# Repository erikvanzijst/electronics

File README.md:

# electronics

This is a Pages repo hosted at <https://erikvanzijst.github.io/electronics>.

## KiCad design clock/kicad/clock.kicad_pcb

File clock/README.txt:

https://www.eevblog.com/forum/beginners/using-a-32-768khz-crystal-with-4060-frequency-divider/

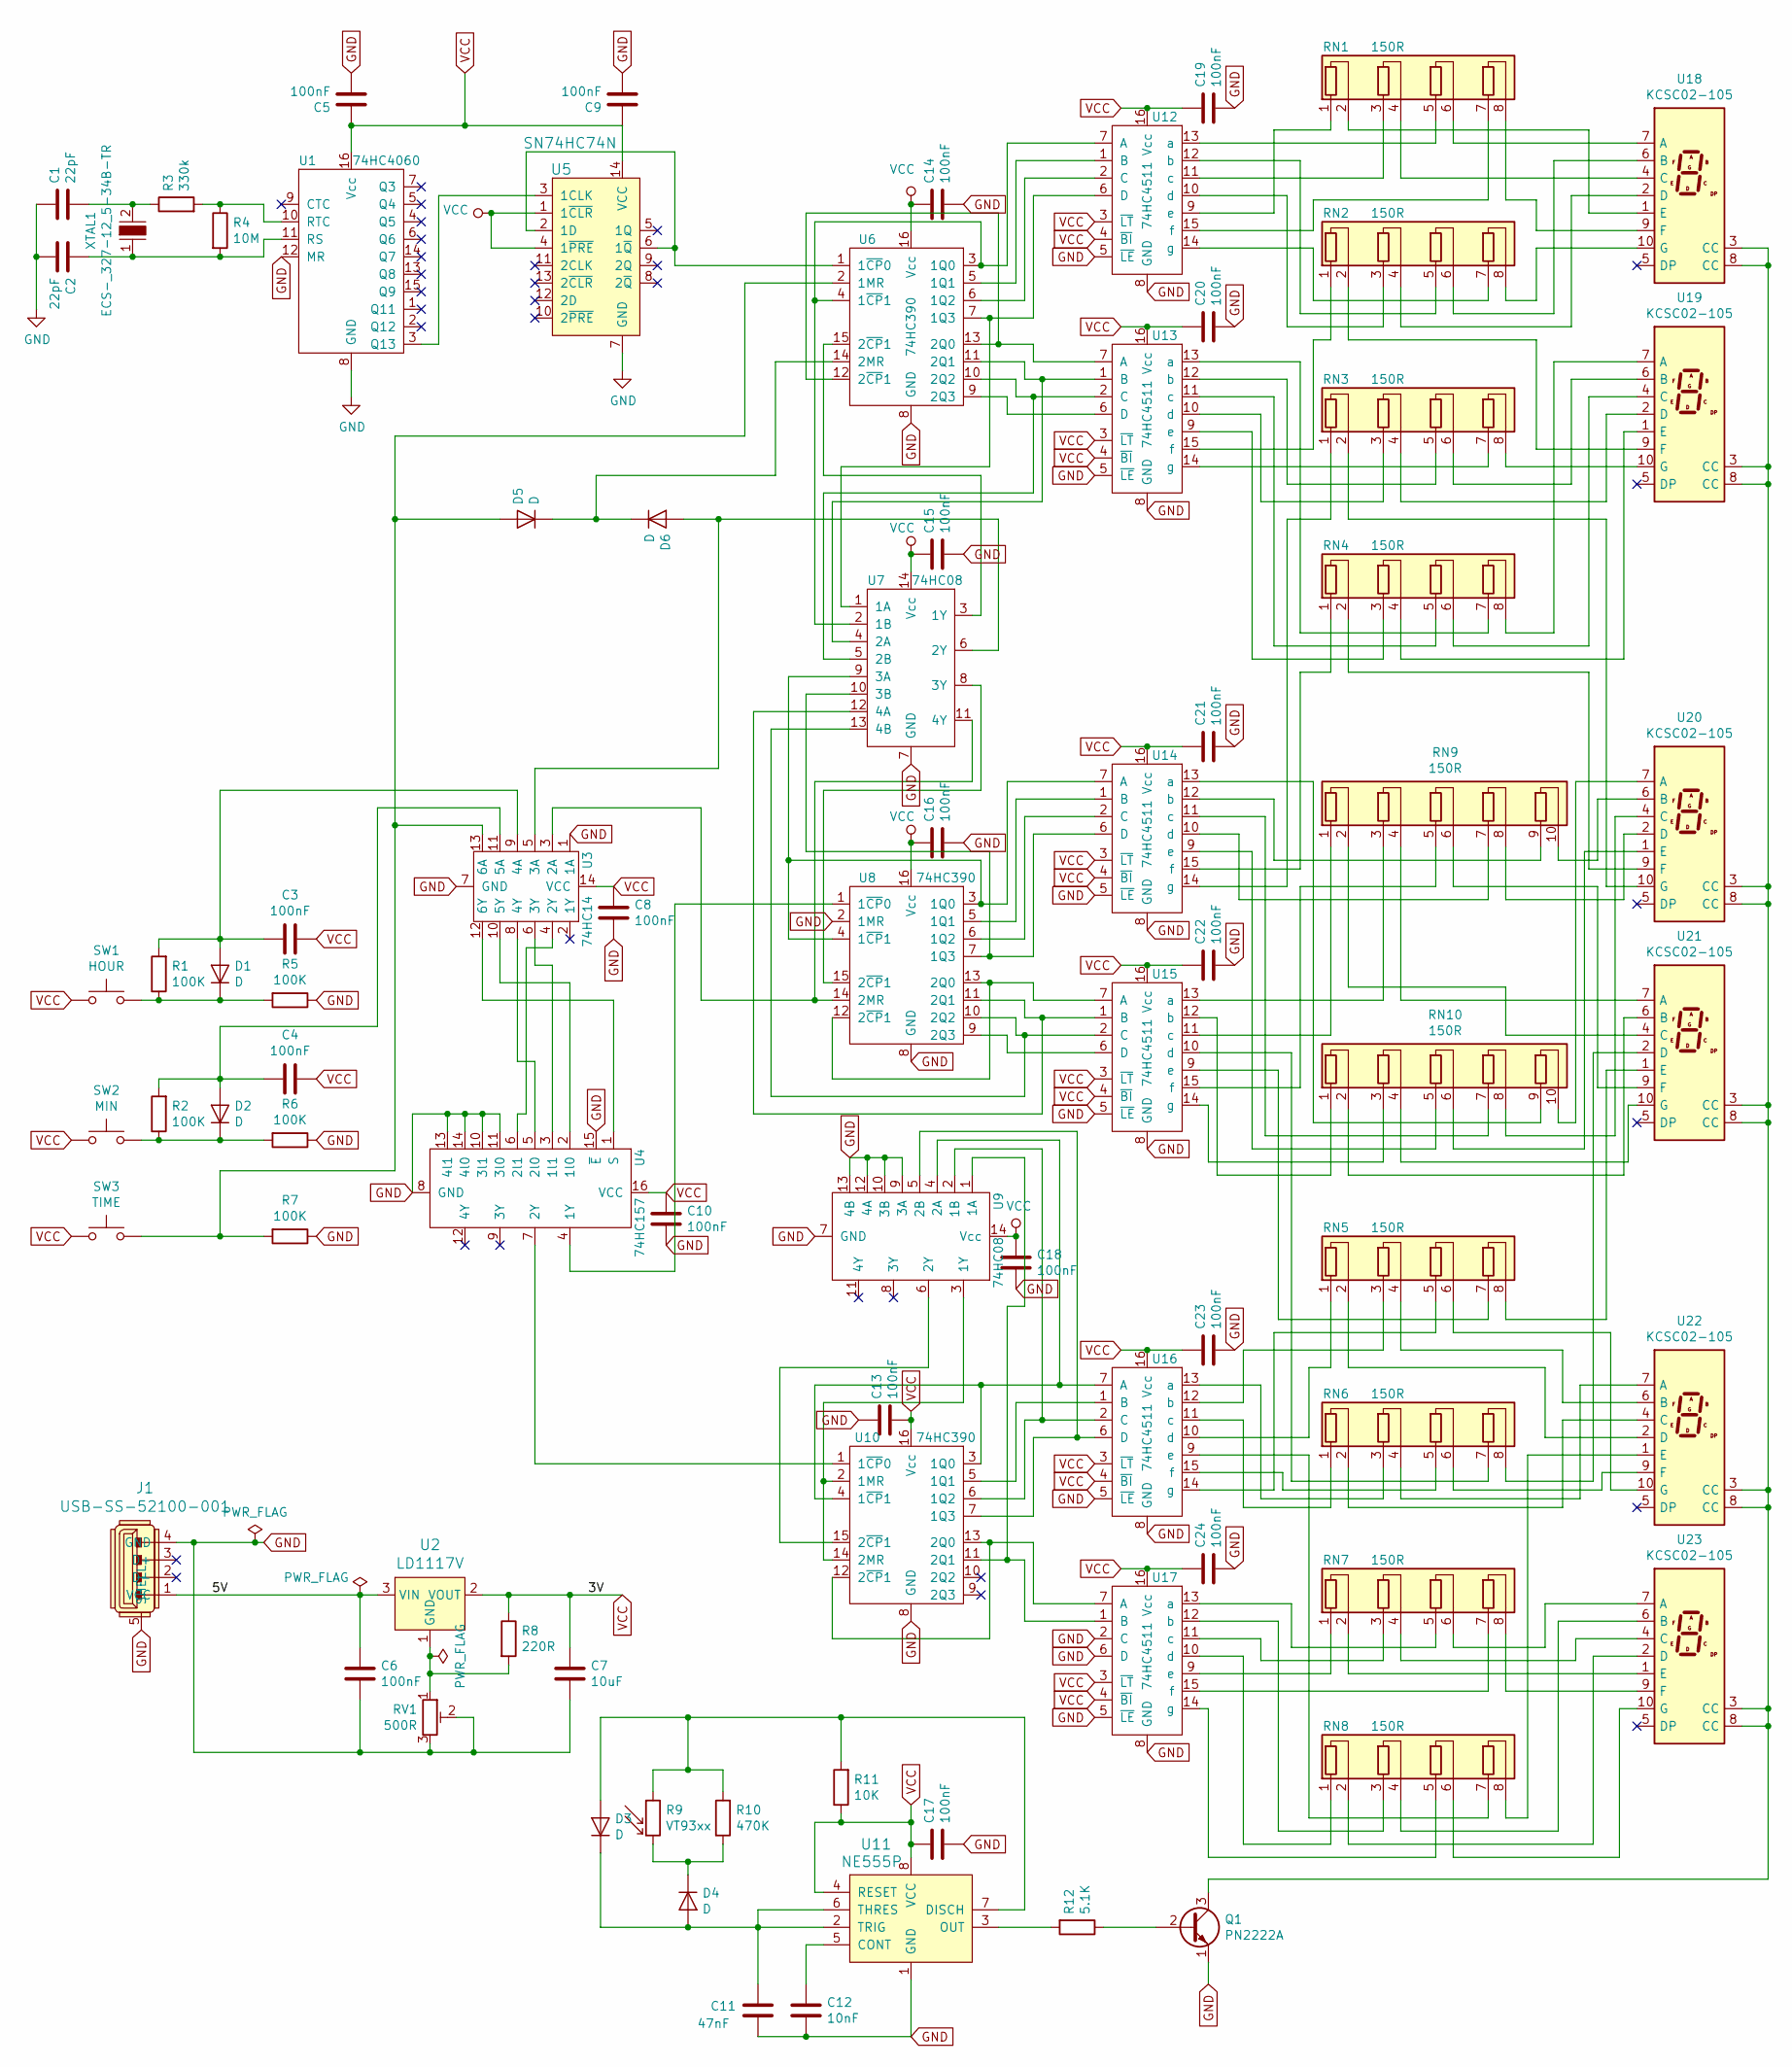
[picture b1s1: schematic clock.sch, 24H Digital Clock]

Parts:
C1, C2: 22pF; C_Disc_D5.0mm_W2.5mm_P2.50mm
C3, C4, C5, C6, C8, C9, C10, C13, C14, C15, C16, C17, C18, C19, C20, C21, C22, C23, C24: 100nF; C_Disc_D5.0mm_W2.5mm_P2.50mm
C7: 10uF; C_Radial_D5.0mm_H11.0mm_P2.00mm
C11: 47nF; C_Disc_D5.0mm_W2.5mm_P2.50mm
C12: 10nF; C_Disc_D5.0mm_W2.5mm_P2.50mm
D1, D2, D3, D4, D5, D6: D; Diode_DO-35_P10mm
J1: USB-SS-52100-001; USB_A_Stewart_SS-52100-001_Horizontal; MPN SS-52100-001; Digi-Key_PN 380-1412-ND
Q1: PN2222A; TO-92_Inline_Wide
R1, R2, R5, R6, R7: 100K; R_Axial_DIN0207_L6.3mm_D2.5mm_P7.62mm_Horizontal
R3: 330k; R_Axial_DIN0207_L6.3mm_D2.5mm_P7.62mm_Horizontal
R4: 10M; R_Axial_DIN0207_L6.3mm_D2.5mm_P7.62mm_Horizontal
R8: 220R; R_Axial_DIN0207_L6.3mm_D2.5mm_P7.62mm_Horizontal
R9: VT93xx; R_LDR_4.9x4.2mm_P2.54mm_Vertical
R10: 470K; R_Axial_DIN0207_L6.3mm_D2.5mm_P7.62mm_Horizontal
R11: 10K; R_Axial_DIN0207_L6.3mm_D2.5mm_P7.62mm_Horizontal
R12: 5.1K; R_Axial_DIN0207_L6.3mm_D2.5mm_P7.62mm_Horizontal
RN1, RN2, RN3, RN4, RN5, RN6, RN7, RN8: 150R; R_Array_SIP8
RN9, RN10: 150R; R_Array_SIP10
RV1: 500R; Potentiometer_Bourns_3339P_Vertical_HandSoldering
SW1: HOUR; SW_PUSH_6mm_H4.3mm
SW2: MIN; SW_PUSH_6mm_H4.3mm
SW3: TIME; SW_PUSH_6mm_H4.3mm
U1: 74HC4060; DIP-16_W7.62mm_Socket
U2: LD1117V; TO-220-3; MPN LD1117V; Digi-Key_PN 497-7310-5-ND
U3: 74HC14; Socket_DIP-14_0.775in_Conn
U4: 74HC157; DIP-16_W7.62mm_Socket
U5: SN74HC74N; Socket_DIP-14_0.775in_Conn; MPN SN74HC74N; Digi-Key_PN 296-1602-5-ND
U6, U8, U10: 74HC390; DIP-16_W7.62mm_Socket
U7, U9: 74HC08; Socket_DIP-14_0.775in_Conn
U11: NE555P; DIP-8_W7.62mm_Socket; MPN NE555P; Digi-Key_PN 296-1411-5-ND
U12, U13, U14, U15, U16, U17: 74HC4511; DIP-16_W7.62mm_Socket
U18, U19, U20, U21, U22, U23: KCSC02-105; 7SegmentLED_LTS6760_LTS6780
XTAL1: ECS-_327-12_5-34B-TR; Crystal_DS26_D2.0mm_L6.0mm_Horizontal; MPN ECS-.327-12.5-34B-TR; Digi-Key_PN XC1617CT-ND

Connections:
/5V: C6.1, J1.1 (VCC), U2.3 (VIN)
GND: C1.1, C2.2, C5.2, C6.2, C7.2, C8.2, C9.2, C10.2, C11.2, C12.2, C13.1, C14.2, C15.2, C16.2, C17.2, C18.2, C19.2, C20.2, C21.2, C22.2, C23.2, C24.2, J1.4 (GND), J1.5 (SHELL), Q1.1 (E), R5.1, R6.1, R7.1, RV1.2, RV1.3, U1.8 (GND), U1.12 (MR), U3.1 (1A), U3.7 (GND), U4.8 (GND), U4.10 (3l1), U4.11 (3l0), U4.13 (4l1), U4.14 (4l0), U4.15 (~E), U5.7 (GND), U6.8 (GND), U7.7 (GND), U8.2 (1MR), U8.8 (GND), U9.7 (GND), U9.9 (3A), U9.10 (3B), U9.12 (4A), U9.13 (4B), U10.8 (GND), U11.1 (GND), U12.5 (~LE), U12.8 (GND), U13.5 (~LE), U13.8 (GND), U14.5 (~LE), U14.8 (GND), U15.5 (~LE), U15.8 (GND), U16.5 (~LE), U16.8 (GND), U17.2 (C), U17.5 (~LE), U17.6 (D), U17.8 (GND)
unnamed: C1.2, R3.1, XTAL1.2
unnamed: C2.1, R4.2, U1.11 (RS), XTAL1.1
unnamed: C3.2, D1.2 (A), R1.2, U3.9 (4A)
unnamed: C4.2, D2.2 (A), R2.2, U3.11 (5A)
unnamed: C11.1, D3.1 (K), D4.2 (A), U11.2 (TRIG), U11.6 (THRES)
unnamed: C12.1, U11.5 (CONT)
unnamed: D1.1 (K), R1.1, R5.2, SW1.2
unnamed: D2.1 (K), R2.1, R6.2, SW2.2
unnamed: D3.2 (A), R9.1, R10.2, R11.2, U11.7 (DISCH)
unnamed: D4.1 (K), R9.2, R10.1
unnamed: D5.1 (K), D6.1 (K), U6.14 (2MR)
unnamed: D5.2 (A), R7.2, SW3.2, U3.13 (6A), U6.2 (1MR)
unnamed: D6.2 (A), U3.5 (3A), U7.6 (2Y)
unnamed: Q1.2 (B), R12.1
unnamed: Q1.3 (C), U18.3 (CC), U18.8 (CC), U19.3 (CC), U19.8 (CC), U20.3 (CC), U20.8 (CC), U21.3 (CC), U21.8 (CC), U22.3 (CC), U22.8 (CC), U23.3 (CC), U23.8 (CC)
unnamed: R3.2, R4.1, U1.10 (RTC)
unnamed: R8.2, RV1.1, U2.1 (GND)
unnamed: R12.2, U11.3 (OUT)
unnamed: RN1.1 (R1.1), U12.9 (e)
unnamed: RN1.2 (R1.2), U18.1 (E)
unnamed: RN1.3 (R2.1), U12.11 (c)
unnamed: RN1.4 (R2.2), U18.4 (C)
unnamed: RN1.5 (R3.1), U12.13 (a)
unnamed: RN1.6 (R3.2), U18.7 (A)
unnamed: RN1.7 (R4.1), U12.15 (f)
unnamed: RN1.8 (R4.2), U18.9 (F)
unnamed: RN2.1 (R1.1), U13.15 (f)
unnamed: RN2.2 (R1.2), U19.9 (F)
unnamed: RN2.3 (R2.1), U12.10 (d)
unnamed: RN2.4 (R2.2), U18.2 (D)
unnamed: RN2.5 (R3.1), U12.12 (b)
unnamed: RN2.6 (R3.2), U18.6 (B)
unnamed: RN2.7 (R4.1), U12.14 (g)
unnamed: RN2.8 (R4.2), U18.10 (G)
unnamed: RN3.1 (R1.1), U14.14 (g)
unnamed: RN3.2 (R1.2), U20.10 (G)
unnamed: RN3.3 (R2.1), U13.10 (d)
unnamed: RN3.4 (R2.2), U19.2 (D)
unnamed: RN3.5 (R3.1), U13.12 (b)
unnamed: RN3.6 (R3.2), U19.6 (B)
unnamed: RN3.7 (R4.1), U13.14 (g)
unnamed: RN3.8 (R4.2), U19.10 (G)
unnamed: RN4.1 (R1.1), U14.15 (f)
unnamed: RN4.2 (R1.2), U20.9 (F)
unnamed: RN4.3 (R2.1), U13.9 (e)
unnamed: RN4.4 (R2.2), U19.1 (E)
unnamed: RN4.5 (R3.1), U13.11 (c)
unnamed: RN4.6 (R3.2), U19.4 (C)
unnamed: RN4.7 (R4.1), U13.13 (a)
unnamed: RN4.8 (R4.2), U19.7 (A)
unnamed: RN5.1 (R1.1), U16.10 (d)
unnamed: RN5.2 (R1.2), U22.2 (D)
unnamed: RN5.3 (R2.1), U16.12 (b)
unnamed: RN5.4 (R2.2), U22.6 (B)
unnamed: RN5.5 (R3.1), U16.14 (g)
unnamed: RN5.6 (R3.2), U22.10 (G)
unnamed: RN5.7 (R4.1), U15.9 (e)
unnamed: RN5.8 (R4.2), U21.1 (E)
unnamed: RN6.1 (R1.1), U16.11 (c)
unnamed: RN6.2 (R1.2), U22.4 (C)
unnamed: RN6.3 (R2.1), U16.13 (a)
unnamed: RN6.4 (R2.2), U22.7 (A)
unnamed: RN6.5 (R3.1), U16.15 (f)
unnamed: RN6.6 (R3.2), U22.9 (F)
unnamed: RN6.7 (R4.1), U15.10 (d)
unnamed: RN6.8 (R4.2), U21.2 (D)
unnamed: RN7.1 (R1.1), U17.9 (e)
unnamed: RN7.2 (R1.2), U23.1 (E)
unnamed: RN7.3 (R2.1), U17.11 (c)
unnamed: RN7.4 (R2.2), U23.4 (C)
unnamed: RN7.5 (R3.1), U17.13 (a)
unnamed: RN7.6 (R3.2), U23.7 (A)
unnamed: RN7.7 (R4.1), U17.15 (f)
unnamed: RN7.8 (R4.2), U23.9 (F)
unnamed: RN8.1 (R1.1), U17.10 (d)
unnamed: RN8.2 (R1.2), U23.2 (D)
unnamed: RN8.3 (R2.1), U17.12 (b)
unnamed: RN8.4 (R2.2), U23.6 (B)
unnamed: RN8.5 (R3.1), U17.14 (g)
unnamed: RN8.6 (R3.2), U23.10 (G)
unnamed: RN8.7 (R4.1), U16.9 (e)
unnamed: RN8.8 (R4.2), U22.1 (E)
unnamed: RN9.1 (R1.1), U15.11 (c)
unnamed: RN9.2 (R1.2), U21.4 (C)
unnamed: RN9.3 (R2.1), U15.13 (a)
unnamed: RN9.4 (R2.2), U21.7 (A)
unnamed: RN9.5 (R3.1), U15.15 (f)
unnamed: RN9.6 (R3.2), U21.9 (F)
unnamed: RN9.7 (R4.1), U14.10 (d)
unnamed: RN9.8 (R4.2), U20.2 (D)
unnamed: RN9.9 (R5.1), U14.12 (b)
unnamed: RN9.10 (R5.2), U20.6 (B)
unnamed: RN10.1 (R1.1), U15.12 (b)
unnamed: RN10.2 (R1.2), U21.6 (B)
unnamed: RN10.3 (R2.1), U15.14 (g)
unnamed: RN10.4 (R2.2), U21.10 (G)
unnamed: RN10.5 (R3.1), U14.9 (e)
unnamed: RN10.6 (R3.2), U20.1 (E)
unnamed: RN10.7 (R4.1), U14.11 (c)
unnamed: RN10.8 (R4.2), U20.4 (C)
unnamed: RN10.9 (R5.1), U14.13 (a)
unnamed: RN10.10 (R5.2), U20.7 (A)
unnamed: U1.3 (Q13), U5.3 (1CLK)
unnamed: U3.3 (2A), U7.11 (4Y), U8.14 (2MR)
unnamed: U3.4 (2Y), U4.6 (2l1)
unnamed: U3.6 (3Y), U4.3 (1l1)
unnamed: U3.8 (4Y), U4.5 (2l0)
unnamed: U3.10 (5Y), U4.2 (1l0)
unnamed: U3.12 (6Y), U4.1 (S)
unnamed: U4.4 (1Y), U8.1 (1~CP~0)
unnamed: U5.2 (1D), U5.6 (1~Q), U6.1 (1~CP~0)
unnamed: U6.15 (2~CP~1), U7.3 (1Y)
unnamed: U7.8 (3Y), U8.15 (2~CP~1)
unnamed: U4.7 (2Y), U10.1 (1~CP~0)
unnamed: U9.4 (2A), U10.3 (1Q0), U10.4 (1~CP~1), U16.7 (A)
unnamed: U10.5 (1Q1), U16.1 (B)
unnamed: U9.2 (1B), U10.6 (1Q2), U16.2 (C)
unnamed: U9.5 (2B), U10.7 (1Q3), U16.6 (D)
unnamed: U9.1 (1A), U10.11 (2Q1), U17.1 (B)
unnamed: U10.12 (2~CP~1), U10.13 (2Q0), U17.7 (A)
unnamed: U9.3 (1Y), U10.2 (1MR), U10.14 (2MR)
unnamed: U9.6 (2Y), U10.15 (2~CP~1)
unnamed: U6.5 (1Q1), U12.1 (B)
unnamed: U6.6 (1Q2), U12.2 (C)
unnamed: U6.7 (1Q3), U7.1 (1A), U12.6 (D)
unnamed: U6.3 (1Q0), U6.4 (1~CP~1), U7.2 (1B), U12.7 (A)
unnamed: U6.11 (2Q1), U7.4 (2A), U13.1 (B)
unnamed: U6.10 (2Q2), U7.5 (2B), U13.2 (C)
unnamed: U6.9 (2Q3), U13.6 (D)
unnamed: U6.12 (2~CP~1), U6.13 (2Q0), U13.7 (A)
unnamed: U8.5 (1Q1), U14.1 (B)
unnamed: U8.6 (1Q2), U14.2 (C)
unnamed: U7.10 (3B), U8.7 (1Q3), U14.6 (D)
unnamed: U7.9 (3A), U8.3 (1Q0), U8.4 (1~CP~1), U14.7 (A)
unnamed: U7.12 (4A), U8.11 (2Q1), U15.1 (B)
unnamed: U7.13 (4B), U8.10 (2Q2), U15.2 (C)
unnamed: U8.9 (2Q3), U15.6 (D)
unnamed: U8.12 (2~CP~1), U8.13 (2Q0), U15.7 (A)
VCC: C3.1, C4.1, C5.1, C7.1, C8.1, C9.1, C10.1, C13.2, C14.1, C15.1, C16.1, C17.1, C18.1, C19.1, C20.1, C21.1, C22.1, C23.1, C24.1, R8.1, R11.1, SW1.1, SW2.1, SW3.1, U1.16 (Vcc), U2.2 (VOUT), U3.14 (VCC), U4.16 (VCC), U5.1 (1~CLR), U5.4 (1~PRE), U5.14 (VCC), U6.16 (Vcc), U7.14 (Vcc), U8.16 (Vcc), U9.14 (Vcc), U10.16 (Vcc), U11.4 (RESET), U11.8 (VCC), U12.3 (~LT), U12.4 (~BI), U12.16 (Vcc), U13.3 (~LT), U13.4 (~BI), U13.16 (Vcc), U14.3 (~LT), U14.4 (~BI), U14.16 (Vcc), U15.3 (~LT), U15.4 (~BI), U15.16 (Vcc), U16.3 (~LT), U16.4 (~BI), U16.16 (Vcc), U17.3 (~LT), U17.4 (~BI), U17.16 (Vcc)

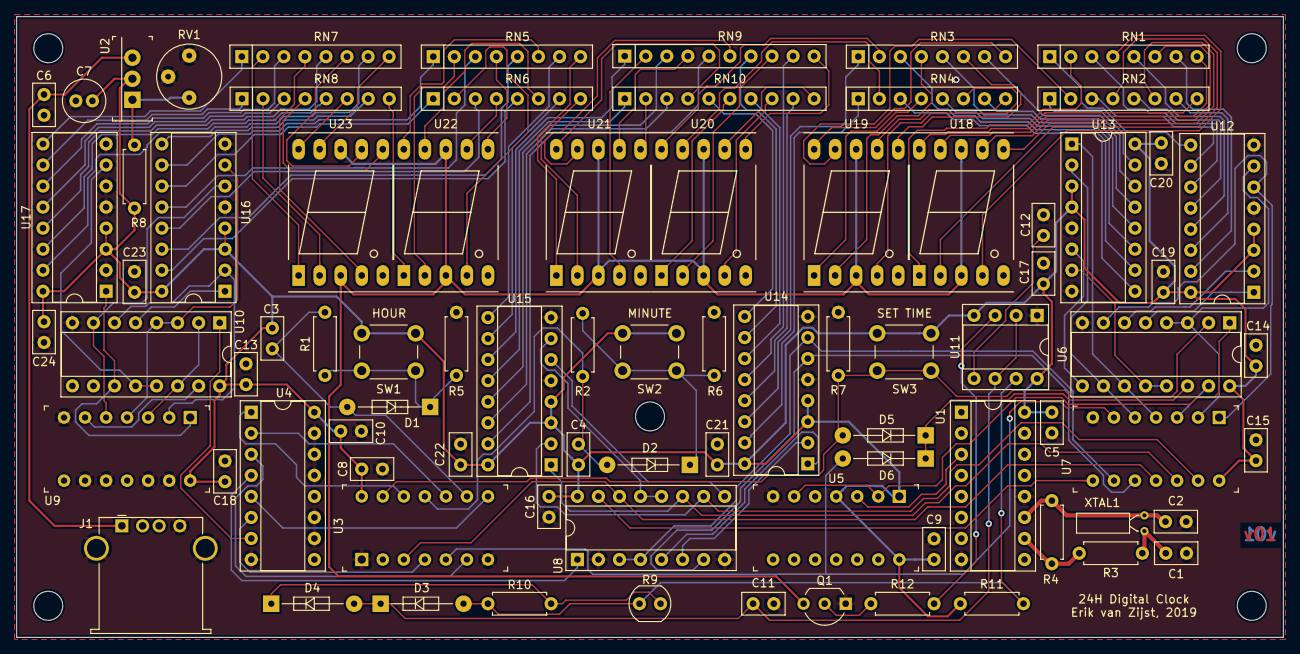
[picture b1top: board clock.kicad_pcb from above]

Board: 2 copper layers, 152.9 x 74.9 mm, 82 parts (0 on the bottom side), 141 nets.

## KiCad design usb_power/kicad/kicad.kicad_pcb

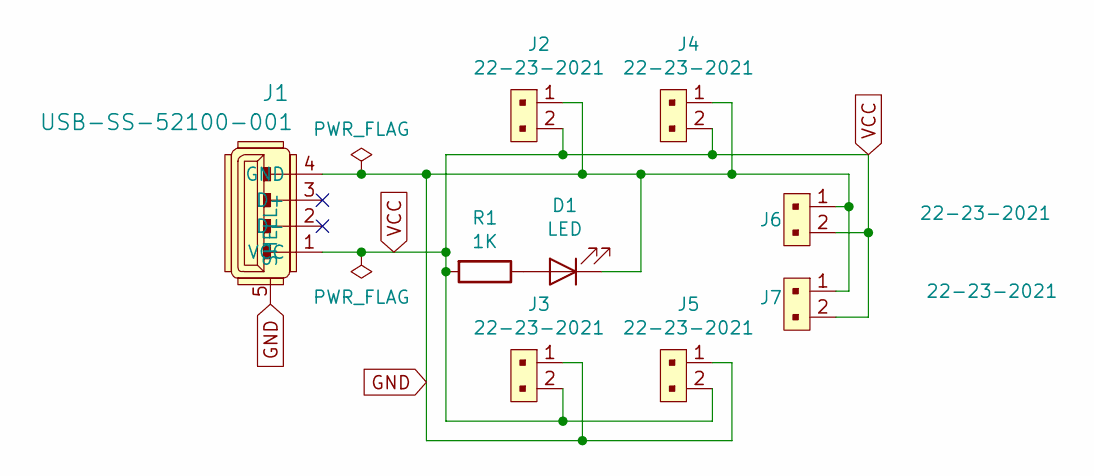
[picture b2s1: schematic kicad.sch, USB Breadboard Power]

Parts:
D1: LED; LED_D5.0mm_IRGrey
J1: USB-SS-52100-001; USB_A_Stewart_SS-52100-001_Horizontal; MPN SS-52100-001; Digi-Key_PN 380-1412-ND
J2, J3, J4, J5, J6, J7: 22-23-2021; PinHeader_1x2_P2.54mm_Drill1.02mm; MPN 22-23-2021; Digi-Key_PN WM4200-ND
R1: 1K; R_Axial_DIN0207_L6.3mm_D2.5mm_P7.62mm_Horizontal

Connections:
GND: D1.1 (K), J1.4 (GND), J1.5 (SHELL), J2.1, J3.1, J4.1, J5.1, J6.1, J7.1
unnamed: D1.2 (A), R1.1
VCC: J1.1 (VCC), J2.2, J3.2, J4.2, J5.2, J6.2, J7.2, R1.2

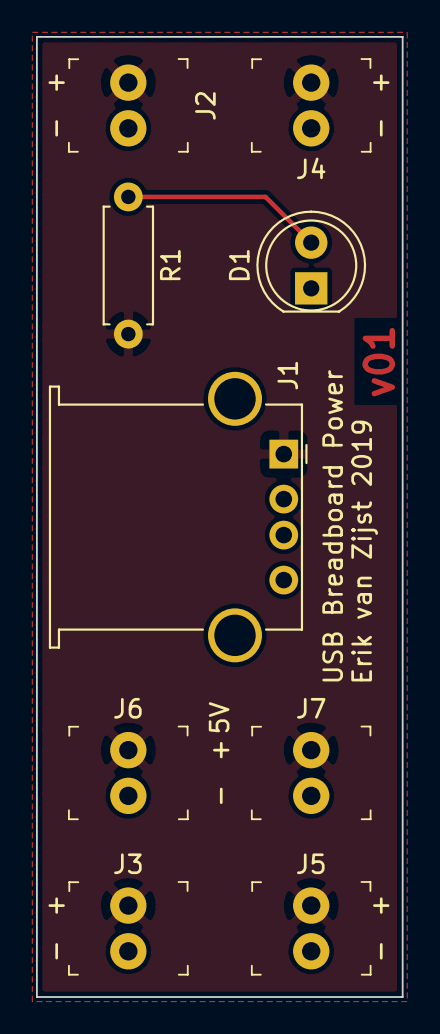
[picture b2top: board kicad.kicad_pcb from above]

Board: 2 copper layers, 20.3 x 53.3 mm, 9 parts (0 on the bottom side), 3 nets.

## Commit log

2019-05-10 Set theme jekyll-theme-slate
2019-06-17 Start of a 24H Digital Clock
2019-06-19 Clock: Created PCB Layout.
2019-06-19 Clock: resize embedded video.
2019-06-20 Clock: Add Gerber files
2019-06-23 Clock: Added Decoupling Capacitors.
2019-07-08 Created new project for USB breadboard power adaptor.
2019-07-11 Clock: Added USB power connector.
2019-07-11 Clock: Added Photoresistor Driven Pulse Width Modulation for 7-Segment Display Brightness.
2019-07-14 Clock: Added decoupling capacitor to 74hc74 flip flop.
    Also added fifth mounting hole in the middle of the board.
2019-07-15 Clock: Isolated Crystal Circuit.
    Also removed the gap between the 7-segment displays of each cluster.
2019-07-20 Clock: Changed footprints for larger ICs.
2019-07-20 Clock: Added adjustable voltage regulator.
    Switched the circuit from 5v to 3v to match the crystal's recommended
    schematic.
2019-07-21 Clock: Added voltage regulator to PCB and switched to resistor networks.
2019-07-22 Clock: Using a 500Ohm trimpot to tune the voltage regulator.
2019-07-27 Clock: Tweak PWM RC values.
2019-07-27 Clock: Changed Resistor Networks to real parts.
2019-07-27 Clock: Adjusted LED load resistor values.
2019-07-28 Clock: Added Bill Of Materials.
2019-07-28 Clock: Fixed diameter center hole.
2019-07-28 Clock: Added missing pulldown resistor to Time button.
2019-07-28 Clock: Time Switch Resets Seconds.
    Added a two-diode OR gate to use the Time switch as a secondary input
    for the seconds counter's reset lines.
2019-07-29 Clock: Switched 24H counter's high digit to quinary counter to match breadboard version.
2019-07-29 Clock: Generated Gerbers.
2019-07-29 Clock: Changed electrolytic capacitor's footprint to polarized one.
2019-07-29 Knight Rider: Created 3D-Printed Base Plate.
2019-07-30 Knight Rider Protoboard: Added 3D-Printed Base Plate.
2019-08-02 Clock: Created a mounting plate for 3D printing.
2019-08-13 Clock: Modified base plate to fit properly.
2019-08-17 Clock MEMS Extension: Created extension board with MEMS oscillator
    This project contains an addon board for the 24H Digital Clock project
    that is mounted over the crystal oscillator section and replaces the
    quartz crystal with a MEMS oscillator IC.
    The oscillator is an LVCMOS SMT device, compatible with the motherboard's
    3v supply and CMOS chips.
2019-09-07 OpAmp ADC: Created an Analog to Digital Convert.
2019-09-07 OpAmps: Updated article.
2019-09-08 OpAmps: Fixed binary representations.
2019-09-16 Scramble: Added marquee circuit description.
2019-09-16 Scramble: Added marquee circuit link.
2019-09-16 Scramble: Resized image.
2019-09-16 Limited the writeup to marquee only, splitting out Scramble as a separate post.
2019-09-16 Matrix Displays: Minor edits.
2019-09-16 Matrix: Minor edits.
2019-09-17 Matrix: Added a paragraph on the data format encoding.
2019-09-17 Scramble: Started blog post.
2019-09-17 Scramble: Added input control.
2019-09-17 Scramble: images.
2019-09-17 Scramble: Adding Power on Reset section.
2019-09-17 Scramble: Added more POR context.
2019-09-17 Scramble: Added dying and restarting logic.
2019-09-18 Scramble: Wrapping up.
2019-09-18 Scramble: Added section on collision race conditions.
2019-09-18 Scramble: Resized logic analyzer screenshots.
2019-09-18 Scramble: Added photo of the final breadboard.
2019-09-18 Scramble: Fixed typo.
2019-09-18 Scramble: Added link to Sparkfun.
2019-10-01 EEPROM: Added first section of the EEPROM Programmer.
2019-10-01 EEPROM: Finished blogpost.
2019-10-01 EEPROM: Added symlink
2019-10-01 EEPROM: Added link to GH resources.
2019-10-01 EEPROM: Minor changes.

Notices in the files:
clock/kicad/clock.kicad_pcb:
License: BY CC 4.0
clock/kicad/clock.sch:
creativecommons.org/licenses/by/4.0
License: CC BY 4.0
